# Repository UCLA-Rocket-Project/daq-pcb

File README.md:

# daq-pcb
DAQ PCB

## Preview
Check out the
[super cool HTML preview](http://ucla-rocket-project.github.io/daq-pcb) .

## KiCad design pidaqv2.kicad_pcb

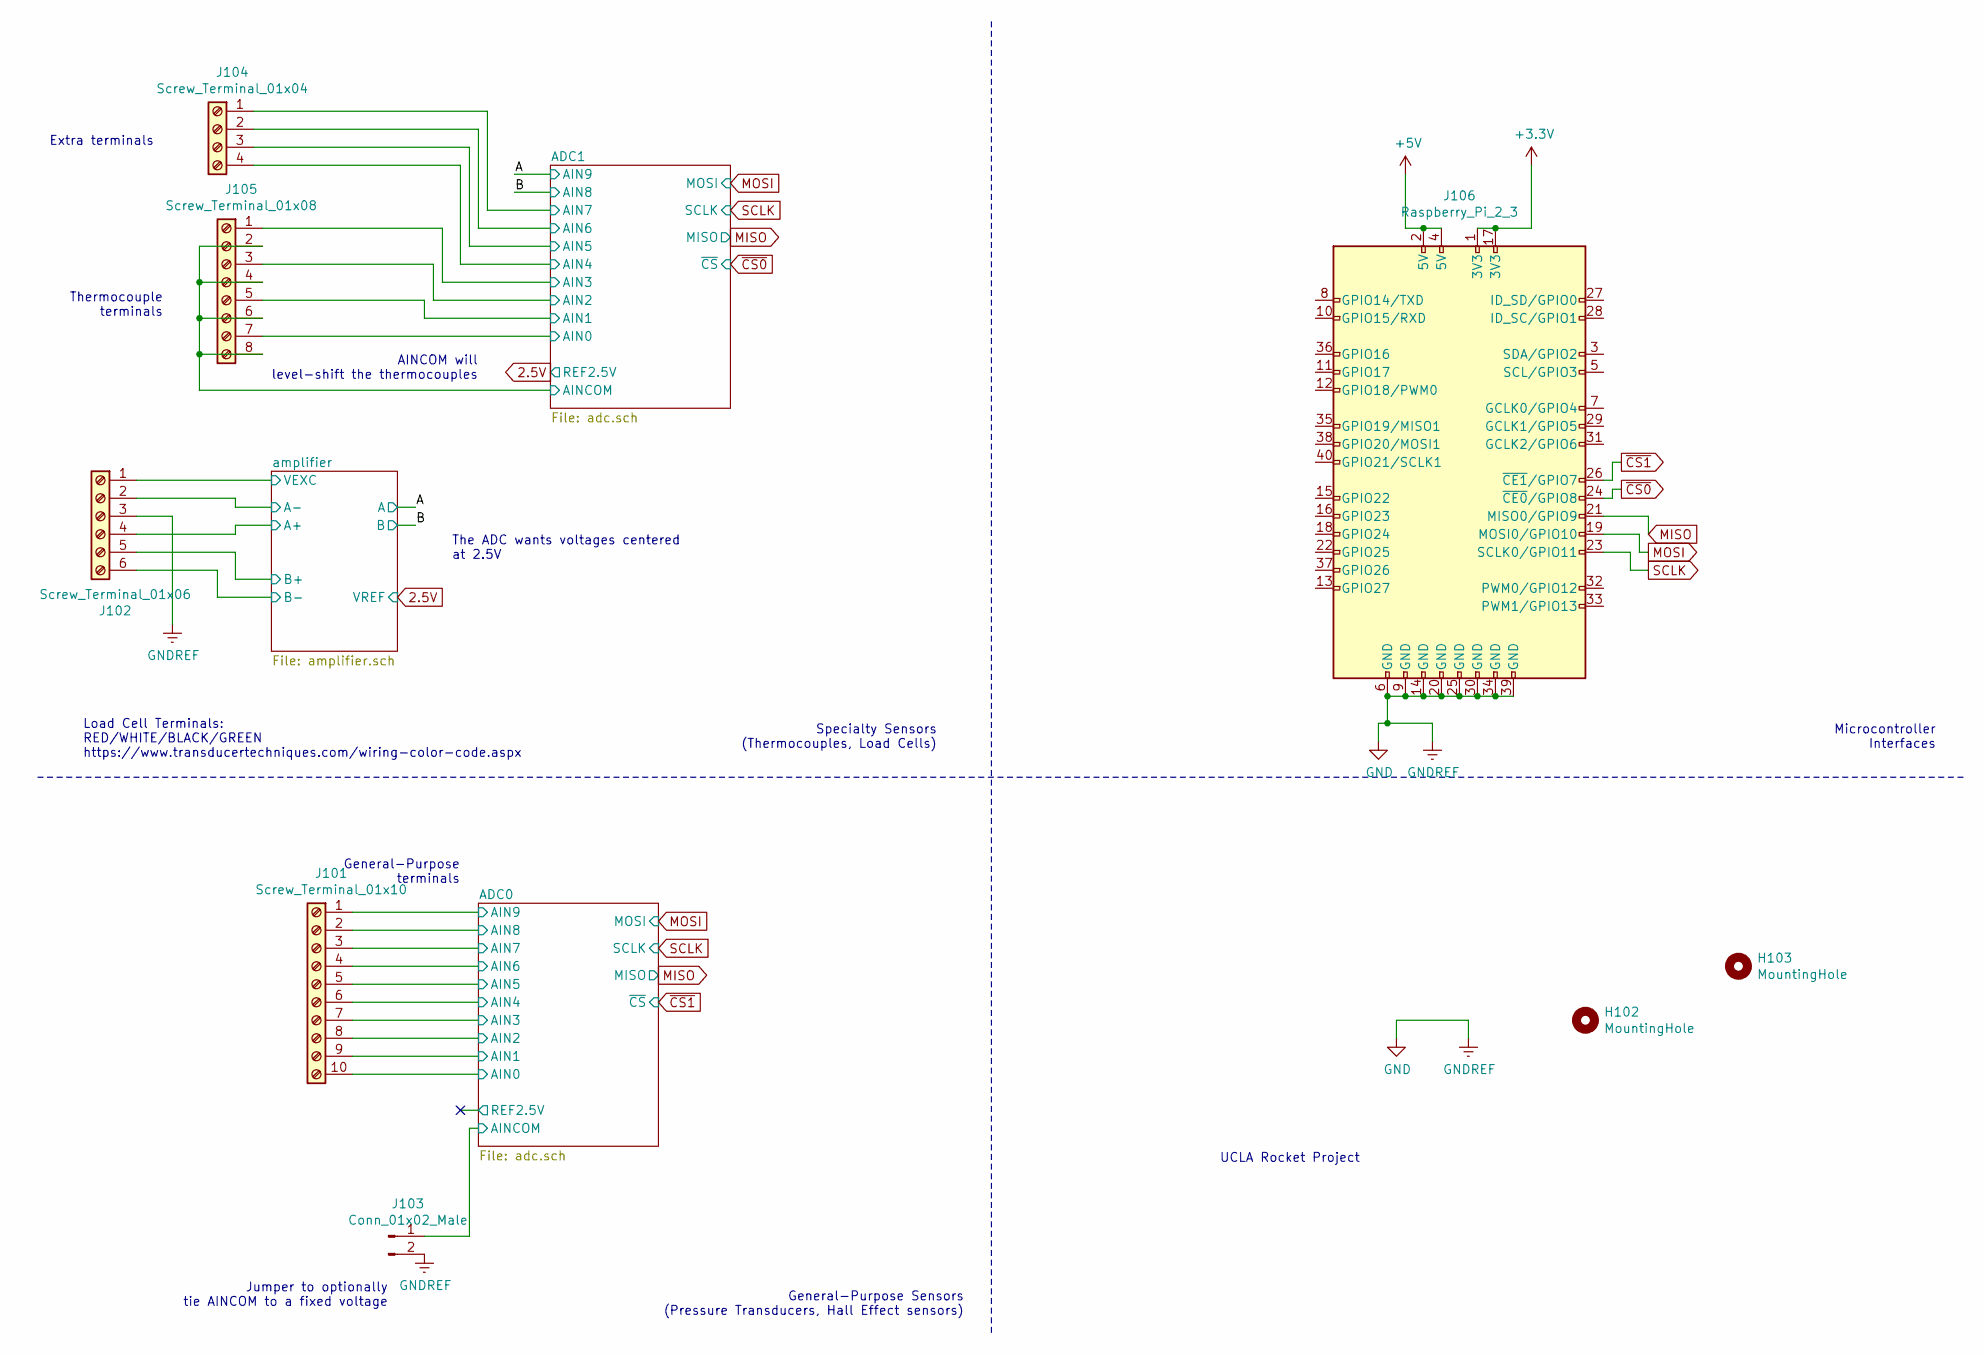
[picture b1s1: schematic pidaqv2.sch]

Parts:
H102, H103: MountingHole; MountingHole_3.2mm_M3_ISO7380
J101: Screw_Terminal_01x10; TerminalBlock_TE_1-282834-0_1x10_P2.54mm_Horizontal
J102: Screw_Terminal_01x06; TerminalBlock_TE_282834-6_1x06_P2.54mm_Horizontal
J103: Conn_01x02_Male; PinHeader_1x02_P2.54mm_Vertical
J104: Screw_Terminal_01x04; TerminalBlock_TE_282834-4_1x04_P2.54mm_Horizontal
J105: Screw_Terminal_01x08; TerminalBlock_TE_282834-8_1x08_P2.54mm_Horizontal
J106: Raspberry_Pi_2_3; PinHeader_2x20_P2.54mm_Vertical

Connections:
+3V3: J106.1 (3V3), J106.17 (3V3); also elsewhere on the board
+5V: J106.2 (5V), J106.4 (5V); also elsewhere on the board
/ADC0/AIN0: J101.10; also elsewhere on the board
/ADC0/AIN1: J101.9; also elsewhere on the board
/ADC0/AIN2: J101.8; also elsewhere on the board
/ADC0/AIN3: J101.7; also elsewhere on the board
/ADC0/AIN4: J101.6; also elsewhere on the board
/ADC0/AIN5: J101.5; also elsewhere on the board
/ADC0/AIN6: J101.4; also elsewhere on the board
/ADC0/AIN7: J101.3; also elsewhere on the board
/ADC0/AIN8: J101.2; also elsewhere on the board
/ADC0/AIN9: J101.1; also elsewhere on the board
/ADC0/AINCOM: J103.1; also elsewhere on the board
/ADC1/AIN0: J105.7; also elsewhere on the board
/ADC1/AIN1: J105.5; also elsewhere on the board
/ADC1/AIN2: J105.3; also elsewhere on the board
/ADC1/AIN3: J105.1; also elsewhere on the board
/ADC1/AIN4: J104.4; also elsewhere on the board
/ADC1/AIN5: J104.3; also elsewhere on the board
/ADC1/AIN6: J104.2; also elsewhere on the board
/ADC1/AIN7: J104.1; also elsewhere on the board
/ADC1/AINCOM: J105.2, J105.4, J105.6, J105.8; also elsewhere on the board
/amplifier/A+: J102.4; also elsewhere on the board
/amplifier/A-: J102.2; also elsewhere on the board
/amplifier/B+: J102.5; also elsewhere on the board
/amplifier/B-: J102.6; also elsewhere on the board
/amplifier/VEXC: J102.1; also elsewhere on the board
GND: J102.3, J103.2, J106.6 (GND), J106.9 (GND), J106.14 (GND), J106.20 (GND), J106.25 (GND), J106.30 (GND), J106.34 (GND), J106.39 (GND); also elsewhere on the board
MISO: J106.21 (MISO0/GPIO9); also elsewhere on the board
MOSI: J106.19 (MOSI0/GPIO10); also elsewhere on the board
SCLK: J106.23 (SCLK0/GPIO11); also elsewhere on the board
~CS0: J106.24 (~CE0~/GPIO8); also elsewhere on the board
~CS1: J106.26 (~CE1~/GPIO7); also elsewhere on the board

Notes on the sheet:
The ADC wants voltages centered at 2.5V
Jumper to optionally tie AINCOM to a fixed voltage
Load Cell Terminals: RED/WHITE/BLACK/GREEN https://www.transducertechniques.com/wiring-color-code.aspx
AINCOM will level-shift the thermocouples
Thermocouple terminals
General-Purpose terminals
UCLA Rocket Project
Specialty Sensors (Thermocouples, Load Cells)
General-Purpose Sensors (Pressure Transducers, Hall Effect sensors)
Microcontroller Interfaces
Extra terminals

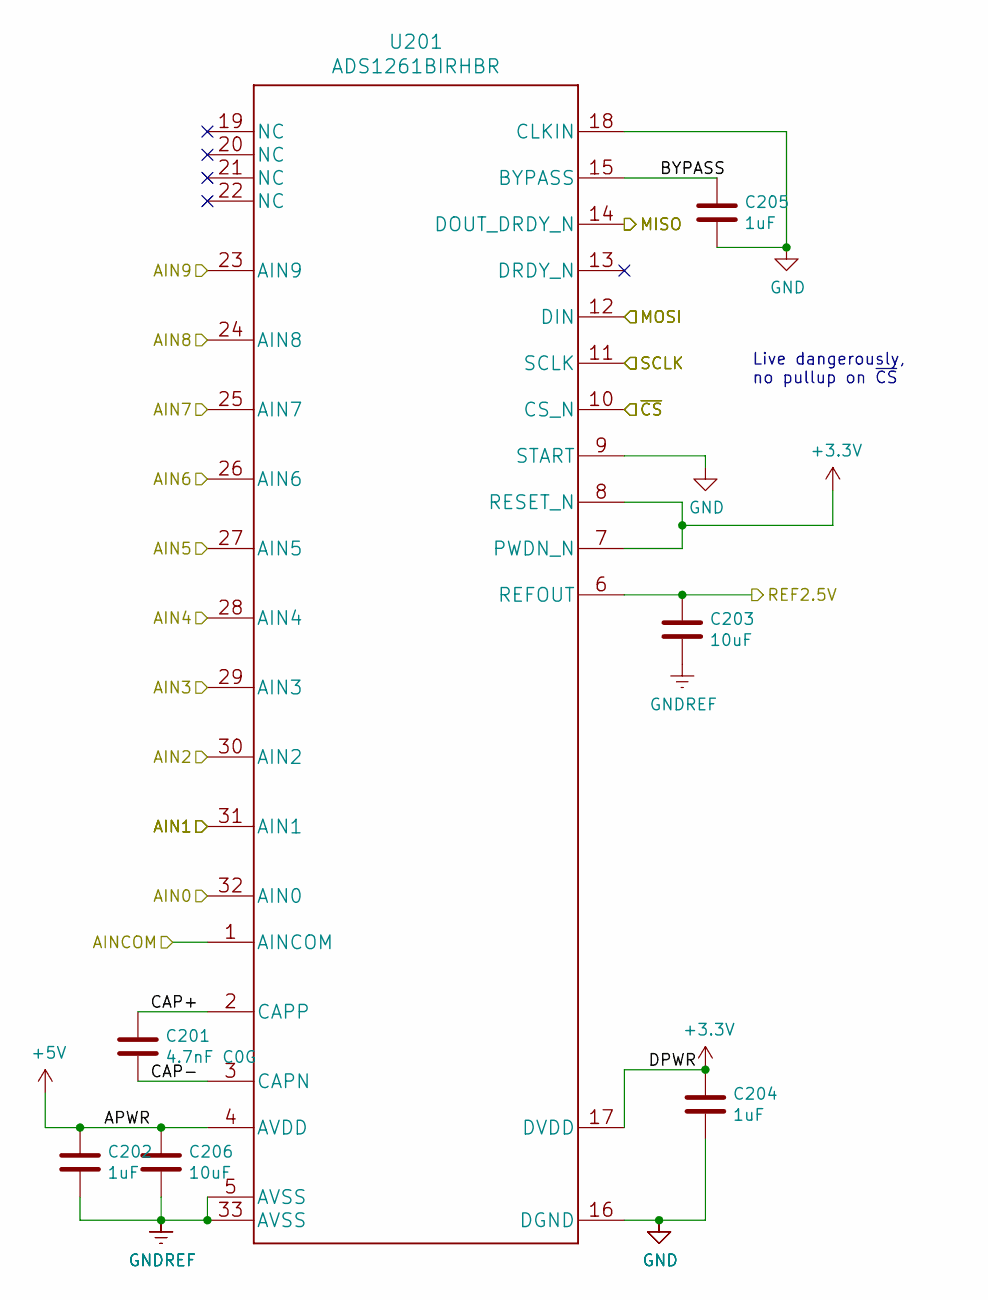
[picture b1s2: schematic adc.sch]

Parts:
C202, C204, C205: 1uF; C_0805_2012Metric_Pad1.15x1.40mm_HandSolder; LCSC C28323
C301: 4.7nF C0G; C_0805_2012Metric_Pad1.15x1.40mm_HandSolder; LCSC C50131
C303, C306: 10uF; C_0805_2012Metric_Pad1.15x1.40mm_HandSolder; LCSC C46653
U301: ADS1261BIRHBR; Texas_S-PVQFN-N32_EP3.45x3.45mm

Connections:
2.5V: C303.1, U301.6 (REFOUT); also elsewhere on the board
+3V3: C204.1, U301.7 (PWDN_N), U301.8 (RESET_N), U301.17 (DVDD); also elsewhere on the board
+5V: C202.1, C306.1, U301.4 (AVDD); also elsewhere on the board
/A: U301.23 (AIN9); also elsewhere on the board
/ADC1/AIN0: U301.32 (AIN0); also elsewhere on the board
/ADC1/AIN1: U301.31 (AIN1); also elsewhere on the board
/ADC1/AIN2: U301.30 (AIN2); also elsewhere on the board
/ADC1/AIN3: U301.29 (AIN3); also elsewhere on the board
/ADC1/AIN4: U301.28 (AIN4); also elsewhere on the board
/ADC1/AIN5: U301.27 (AIN5); also elsewhere on the board
/ADC1/AIN6: U301.26 (AIN6); also elsewhere on the board
/ADC1/AIN7: U301.25 (AIN7); also elsewhere on the board
/ADC1/AINCOM: U301.1 (AINCOM); also elsewhere on the board
/ADC1/CAP+: C301.1, U301.2 (CAPP)
/ADC1/CAP-: C301.2, U301.3 (CAPN)
/B: U301.24 (AIN8); also elsewhere on the board
GND: C202.2, C204.2, C205.2, C303.2, C306.2, U301.5 (AVSS), U301.9 (START), U301.16 (DGND), U301.18 (CLKIN), U301.33 (AVSS); also elsewhere on the board
MISO: U301.14 (DOUT_DRDY_N); also elsewhere on the board
MOSI: U301.12 (DIN); also elsewhere on the board
SCLK: U301.11 (SCLK); also elsewhere on the board
~CS0: U301.10 (CS_N); also elsewhere on the board

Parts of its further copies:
C201: 4.7nF C0G; C_0805_2012Metric_Pad1.15x1.40mm_HandSolder; LCSC C50131
C203, C206: 10uF; C_0805_2012Metric_Pad1.15x1.40mm_HandSolder; LCSC C46653
C302, C304, C305: 1uF; C_0805_2012Metric_Pad1.15x1.40mm_HandSolder; LCSC C28323
U201: ADS1261BIRHBR; Texas_S-PVQFN-N32_EP3.45x3.45mm

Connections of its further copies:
+3V3: C304.1, U201.7 (PWDN_N), U201.8 (RESET_N), U201.17 (DVDD); also elsewhere on the board
+5V: C206.1, C302.1, U201.4 (AVDD); also elsewhere on the board
/ADC0/AIN0: U201.32 (AIN0); also elsewhere on the board
/ADC0/AIN1: U201.31 (AIN1); also elsewhere on the board
/ADC0/AIN2: U201.30 (AIN2); also elsewhere on the board
/ADC0/AIN3: U201.29 (AIN3); also elsewhere on the board
/ADC0/AIN4: U201.28 (AIN4); also elsewhere on the board
/ADC0/AIN5: U201.27 (AIN5); also elsewhere on the board
/ADC0/AIN6: U201.26 (AIN6); also elsewhere on the board
/ADC0/AIN7: U201.25 (AIN7); also elsewhere on the board
/ADC0/AIN8: U201.24 (AIN8); also elsewhere on the board
/ADC0/AIN9: U201.23 (AIN9); also elsewhere on the board
/ADC0/AINCOM: U201.1 (AINCOM); also elsewhere on the board
/ADC0/CAP+: C201.1, U201.2 (CAPP)
/ADC0/CAP-: C201.2, U201.3 (CAPN)
/ADC0/REF2.5V: C203.1, U201.6 (REFOUT)
GND: C203.2, C206.2, C302.2, C304.2, C305.2, U201.5 (AVSS), U201.9 (START), U201.16 (DGND), U201.18 (CLKIN), U201.33 (AVSS); also elsewhere on the board
MISO: U201.14 (DOUT_DRDY_N); also elsewhere on the board
MOSI: U201.12 (DIN); also elsewhere on the board
SCLK: U201.11 (SCLK); also elsewhere on the board
~CS1: U201.10 (CS_N); also elsewhere on the board

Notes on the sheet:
Live dangerously, no pullup on ~CS

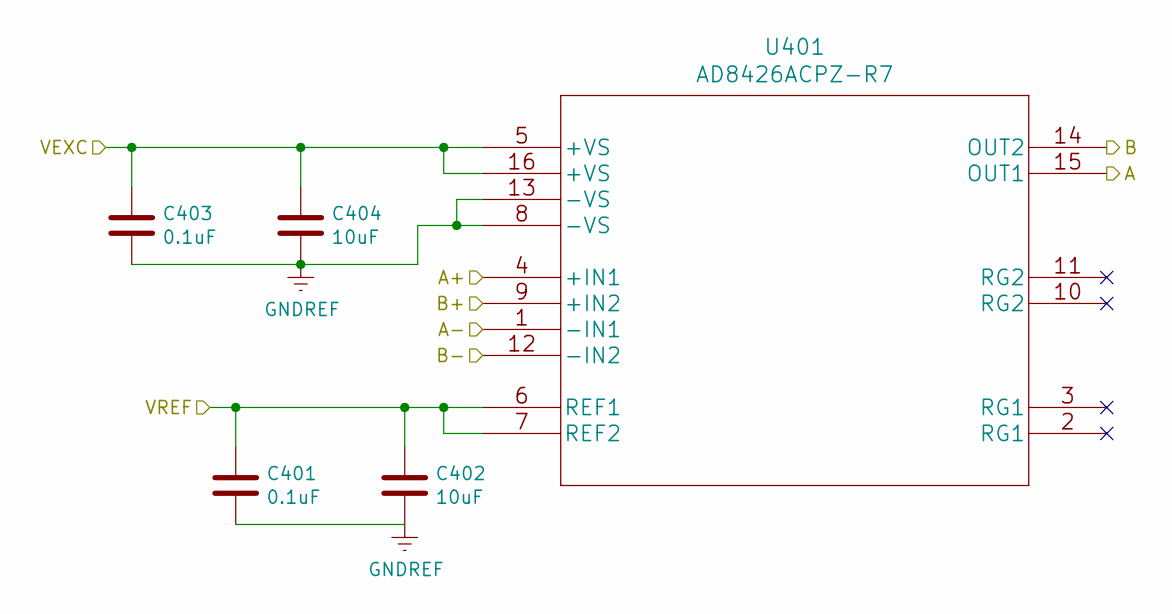
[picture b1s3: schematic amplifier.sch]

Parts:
C401, C403: 0.1uF; C_0805_2012Metric_Pad1.15x1.40mm_HandSolder; LCSC C62912
C402, C404: 10uF; C_0805_2012Metric_Pad1.15x1.40mm_HandSolder; LCSC C46653
U401: AD8426ACPZ-R7

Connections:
2.5V: C401.1, C402.1, U401.6 (REF1), U401.7 (REF2); also elsewhere on the board
/A: U401.15 (OUT1); also elsewhere on the board
/B: U401.14 (OUT2); also elsewhere on the board
/amplifier/A+: U401.4 (+IN1); also elsewhere on the board
/amplifier/A-: U401.1 (-IN1); also elsewhere on the board
/amplifier/B+: U401.9 (+IN2); also elsewhere on the board
/amplifier/B-: U401.12 (-IN2); also elsewhere on the board
/amplifier/VEXC: C403.1, C404.1, U401.5 (+VS), U401.16 (+VS); also elsewhere on the board
GND: C401.2, C402.2, C403.2, C404.2, U401.8 (-VS), U401.13 (-VS); also elsewhere on the board

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
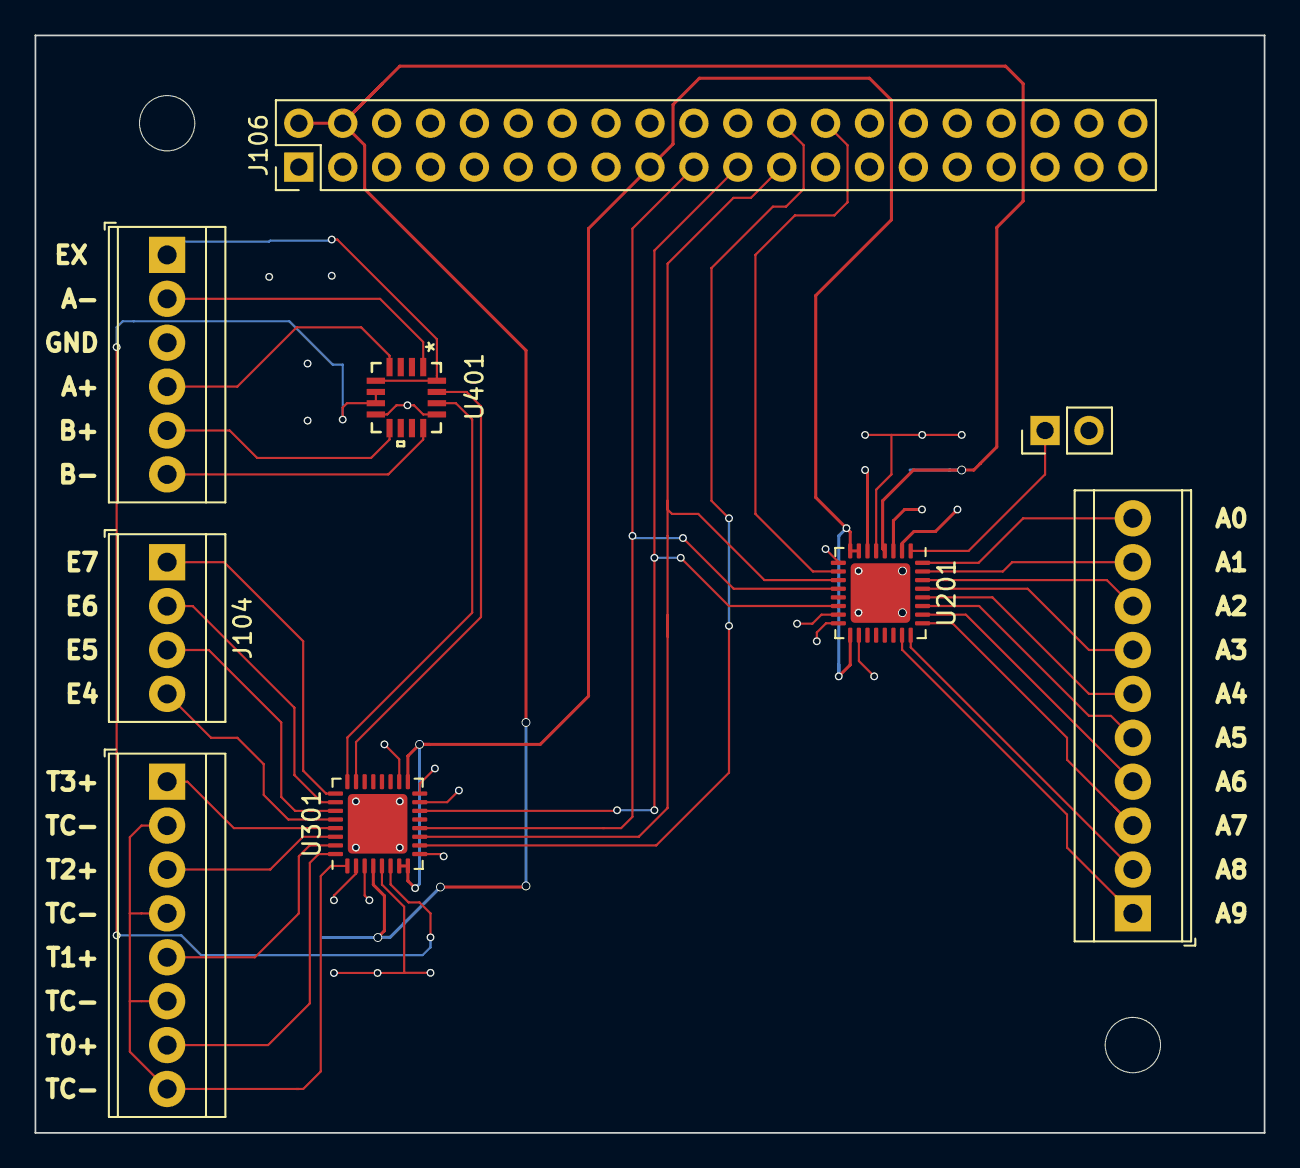
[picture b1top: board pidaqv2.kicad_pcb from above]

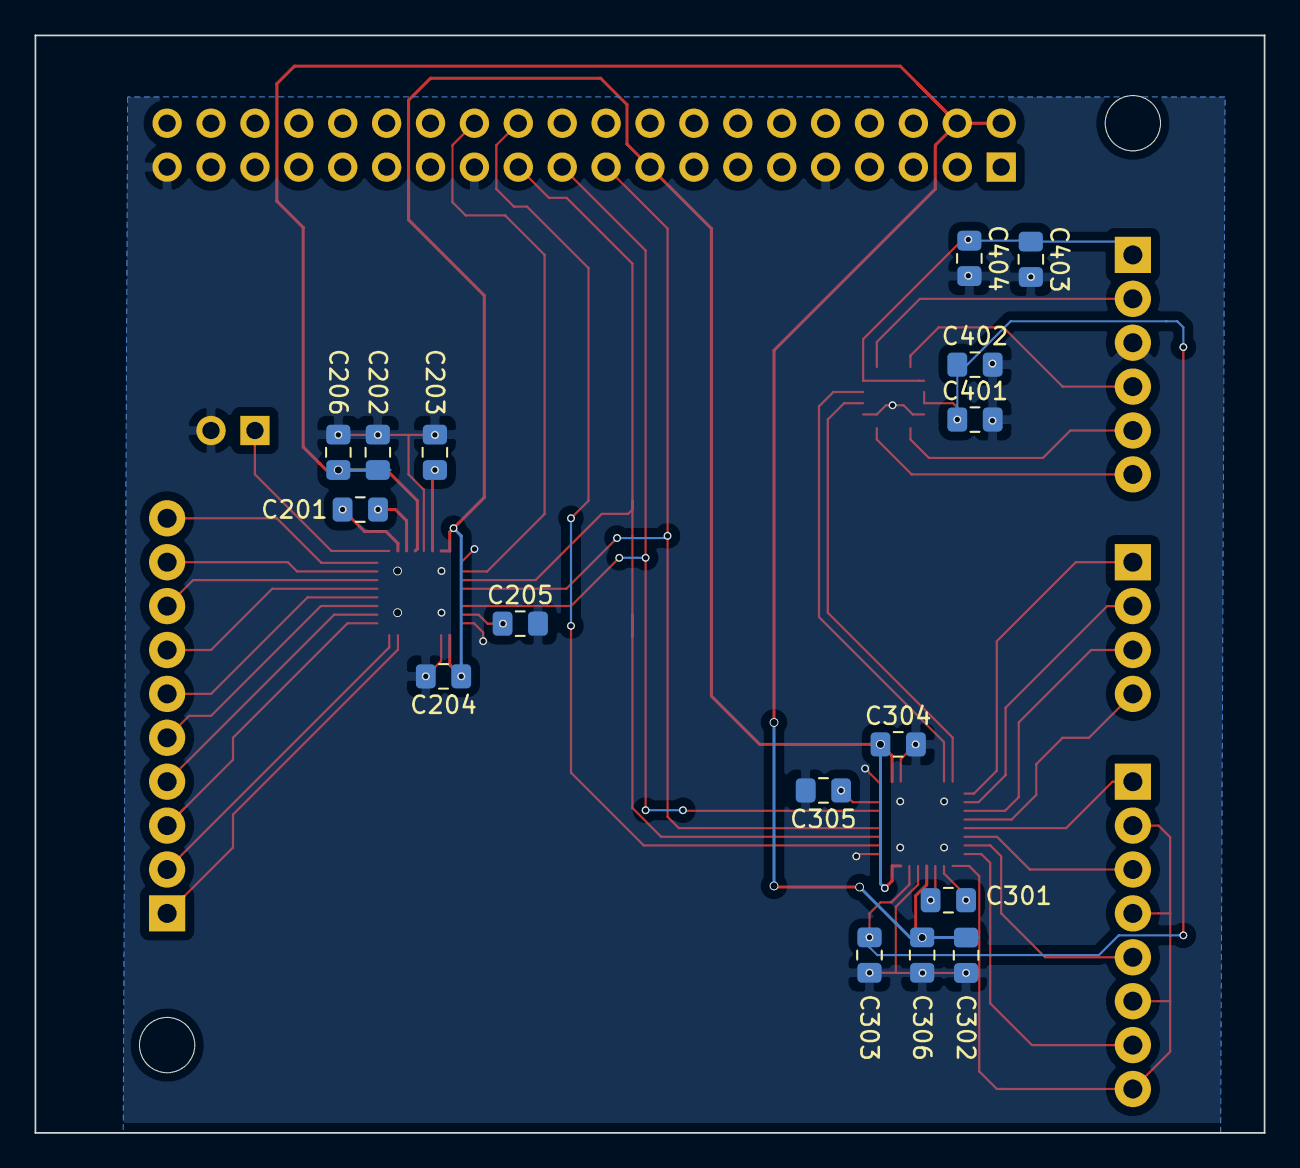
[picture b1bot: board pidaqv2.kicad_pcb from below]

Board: 2 copper layers, 71.1 x 63.5 mm, 27 parts (16 on the bottom side), 43 nets.

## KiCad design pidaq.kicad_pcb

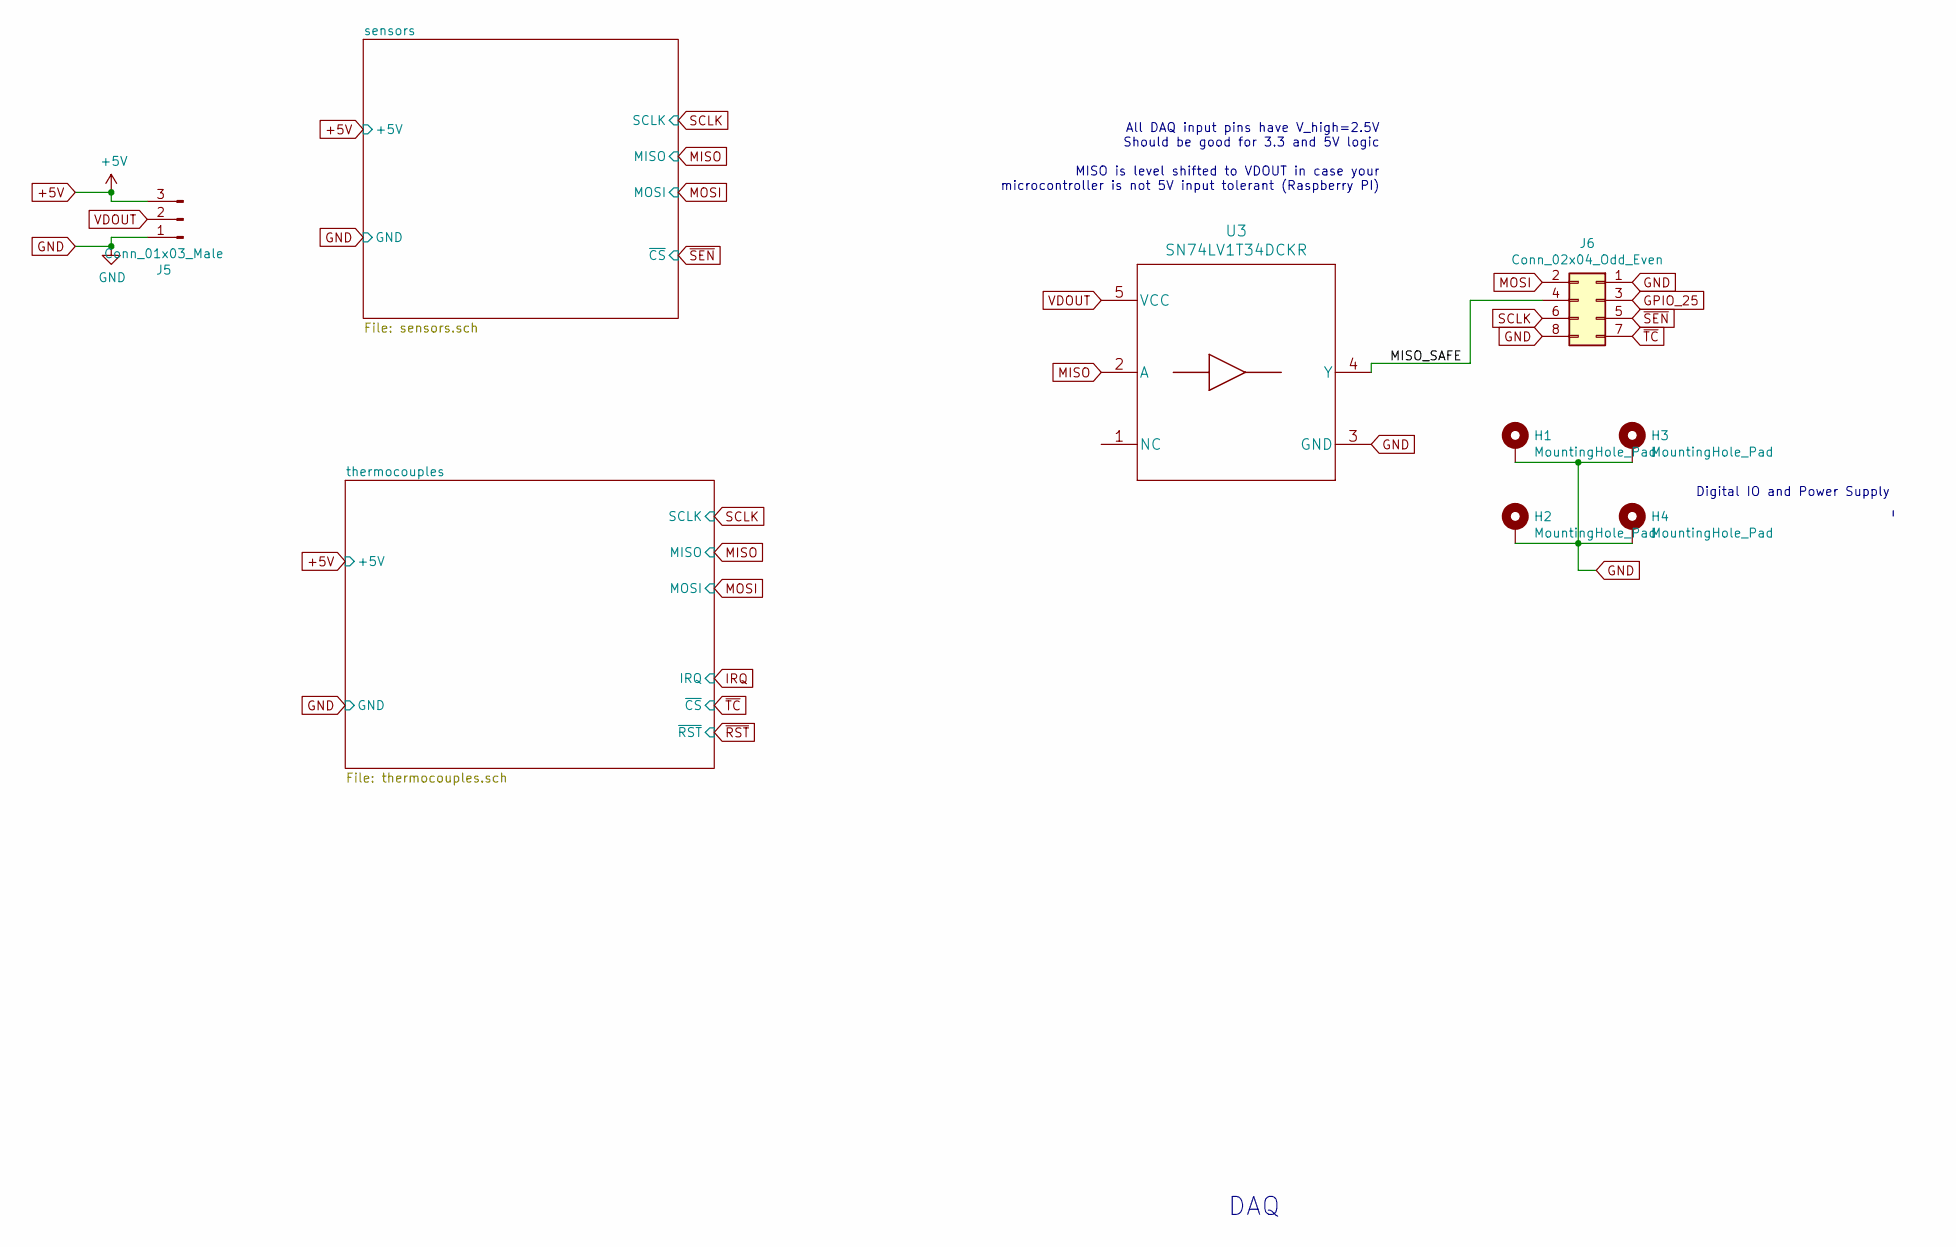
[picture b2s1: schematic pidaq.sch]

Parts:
H1, H2, H3, H4: MountingHole_Pad; MountingHole_3.2mm_M3_Pad_Via
J5: Conn_01x03_Male; PinHeader_1x03_P2.54mm_Vertical
J6: Conn_02x04_Odd_Even; PinSocket_2x04_P2.54mm_Vertical
U3: SN74LV1T34DCKR

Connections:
+5V: J5.3; also elsewhere on the board
/MISO_SAFE: J6.4, U3.4 (Y)
GND: H1.1, H2.1, H3.1, H4.1, J5.1, J6.1, J6.8, U3.3 (GND); also elsewhere on the board
MISO: U3.2 (A); also elsewhere on the board
MOSI: J6.2; also elsewhere on the board
SCLK: J6.6; also elsewhere on the board
VDOUT: J5.2, U3.5 (VCC)
~SEN: J6.5; also elsewhere on the board
~TC: J6.7; also elsewhere on the board

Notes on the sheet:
DAQ
Digital IO and Power Supply
All DAQ input pins have V_high=2.5V Should be good for 3.3 and 5V logic MISO is level shifted to VDOUT in case your microcontroller is not 5V input tolerant (Raspberry PI)

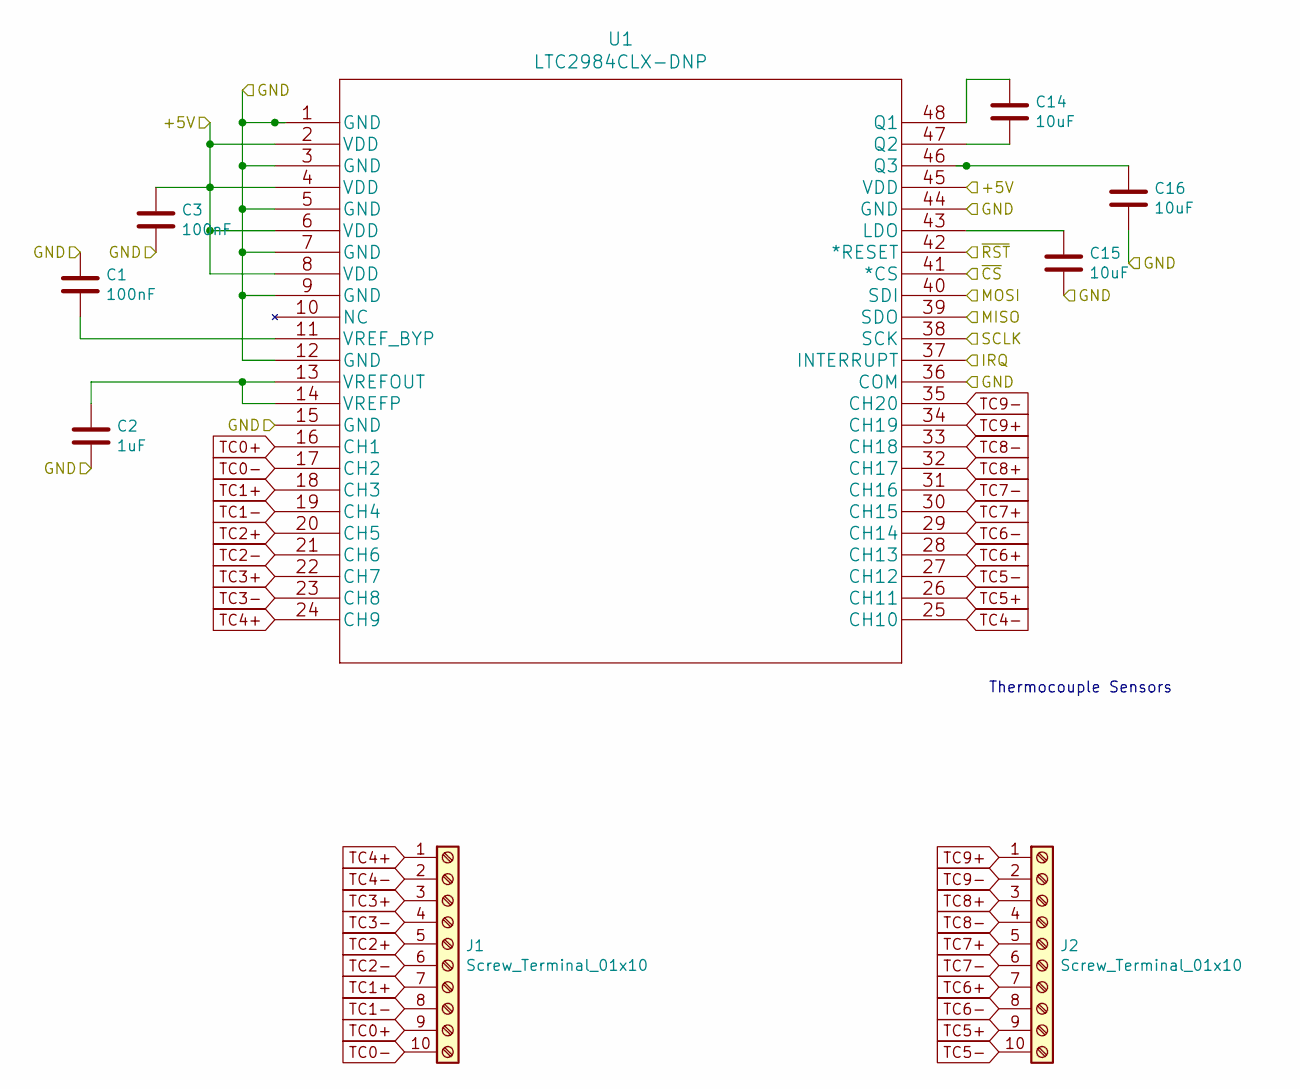
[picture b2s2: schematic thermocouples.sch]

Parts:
C1, C3: 100nF; C_0805_2012Metric_Pad1.15x1.40mm_HandSolder
C2: 1uF; C_0805_2012Metric_Pad1.15x1.40mm_HandSolder
C14, C15, C16: 10uF; C_0805_2012Metric_Pad1.15x1.40mm_HandSolder
J1, J2: Screw_Terminal_01x10; TerminalBlock_Phoenix_MPT-0,5-10-2.54_1x10_P2.54mm_Horizont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
U1: LTC2984CLX-DNP; LTC2984CLX-PBF

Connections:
+5V: C3.1, U1.2 (VDD), U1.4 (VDD), U1.6 (VDD), U1.8 (VDD), U1.45 (VDD); also elsewhere on the board
GND: C1.1, C2.2, C3.2, C15.2, C16.2, U1.1 (GND), U1.3 (GND), U1.5 (GND), U1.7 (GND), U1.9 (GND), U1.12 (GND), U1.15 (GND), U1.36 (COM), U1.44 (GND); also elsewhere on the board
MISO: U1.39 (SDO); also elsewhere on the board
MOSI: U1.40 (SDI); also elsewhere on the board
unnamed: C1.2, U1.11 (VREF_BYP)
unnamed: C2.1, U1.13 (VREFOUT), U1.14 (VREFP)
unnamed: C14.1, U1.48 (Q1)
unnamed: C14.2, U1.47 (Q2)
unnamed: C15.1, U1.43 (LDO)
unnamed: C16.1, U1.46 (Q3)
SCLK: U1.38 (SCK); also elsewhere on the board
TC0+: J1.9, U1.16 (CH1)
TC0-: J1.10, U1.17 (CH2)
TC1+: J1.7, U1.18 (CH3)
TC1-: J1.8, U1.19 (CH4)
TC2+: J1.5, U1.20 (CH5)
TC2-: J1.6, U1.21 (CH6)
TC3+: J1.3, U1.22 (CH7)
TC3-: J1.4, U1.23 (CH8)
TC4+: J1.1, U1.24 (CH9)
TC4-: J1.2, U1.25 (CH10)
TC5+: J2.9, U1.26 (CH11)
TC5-: J2.10, U1.27 (CH12)
TC6+: J2.7, U1.28 (CH13)
TC6-: J2.8, U1.29 (CH14)
TC7+: J2.5, U1.30 (CH15)
TC7-: J2.6, U1.31 (CH16)
TC8+: J2.3, U1.32 (CH17)
TC8-: J2.4, U1.33 (CH18)
TC9+: J2.1, U1.34 (CH19)
TC9-: J2.2, U1.35 (CH20)
~TC: U1.41 (*CS); also elsewhere on the board

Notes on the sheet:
Thermocouple Sensors

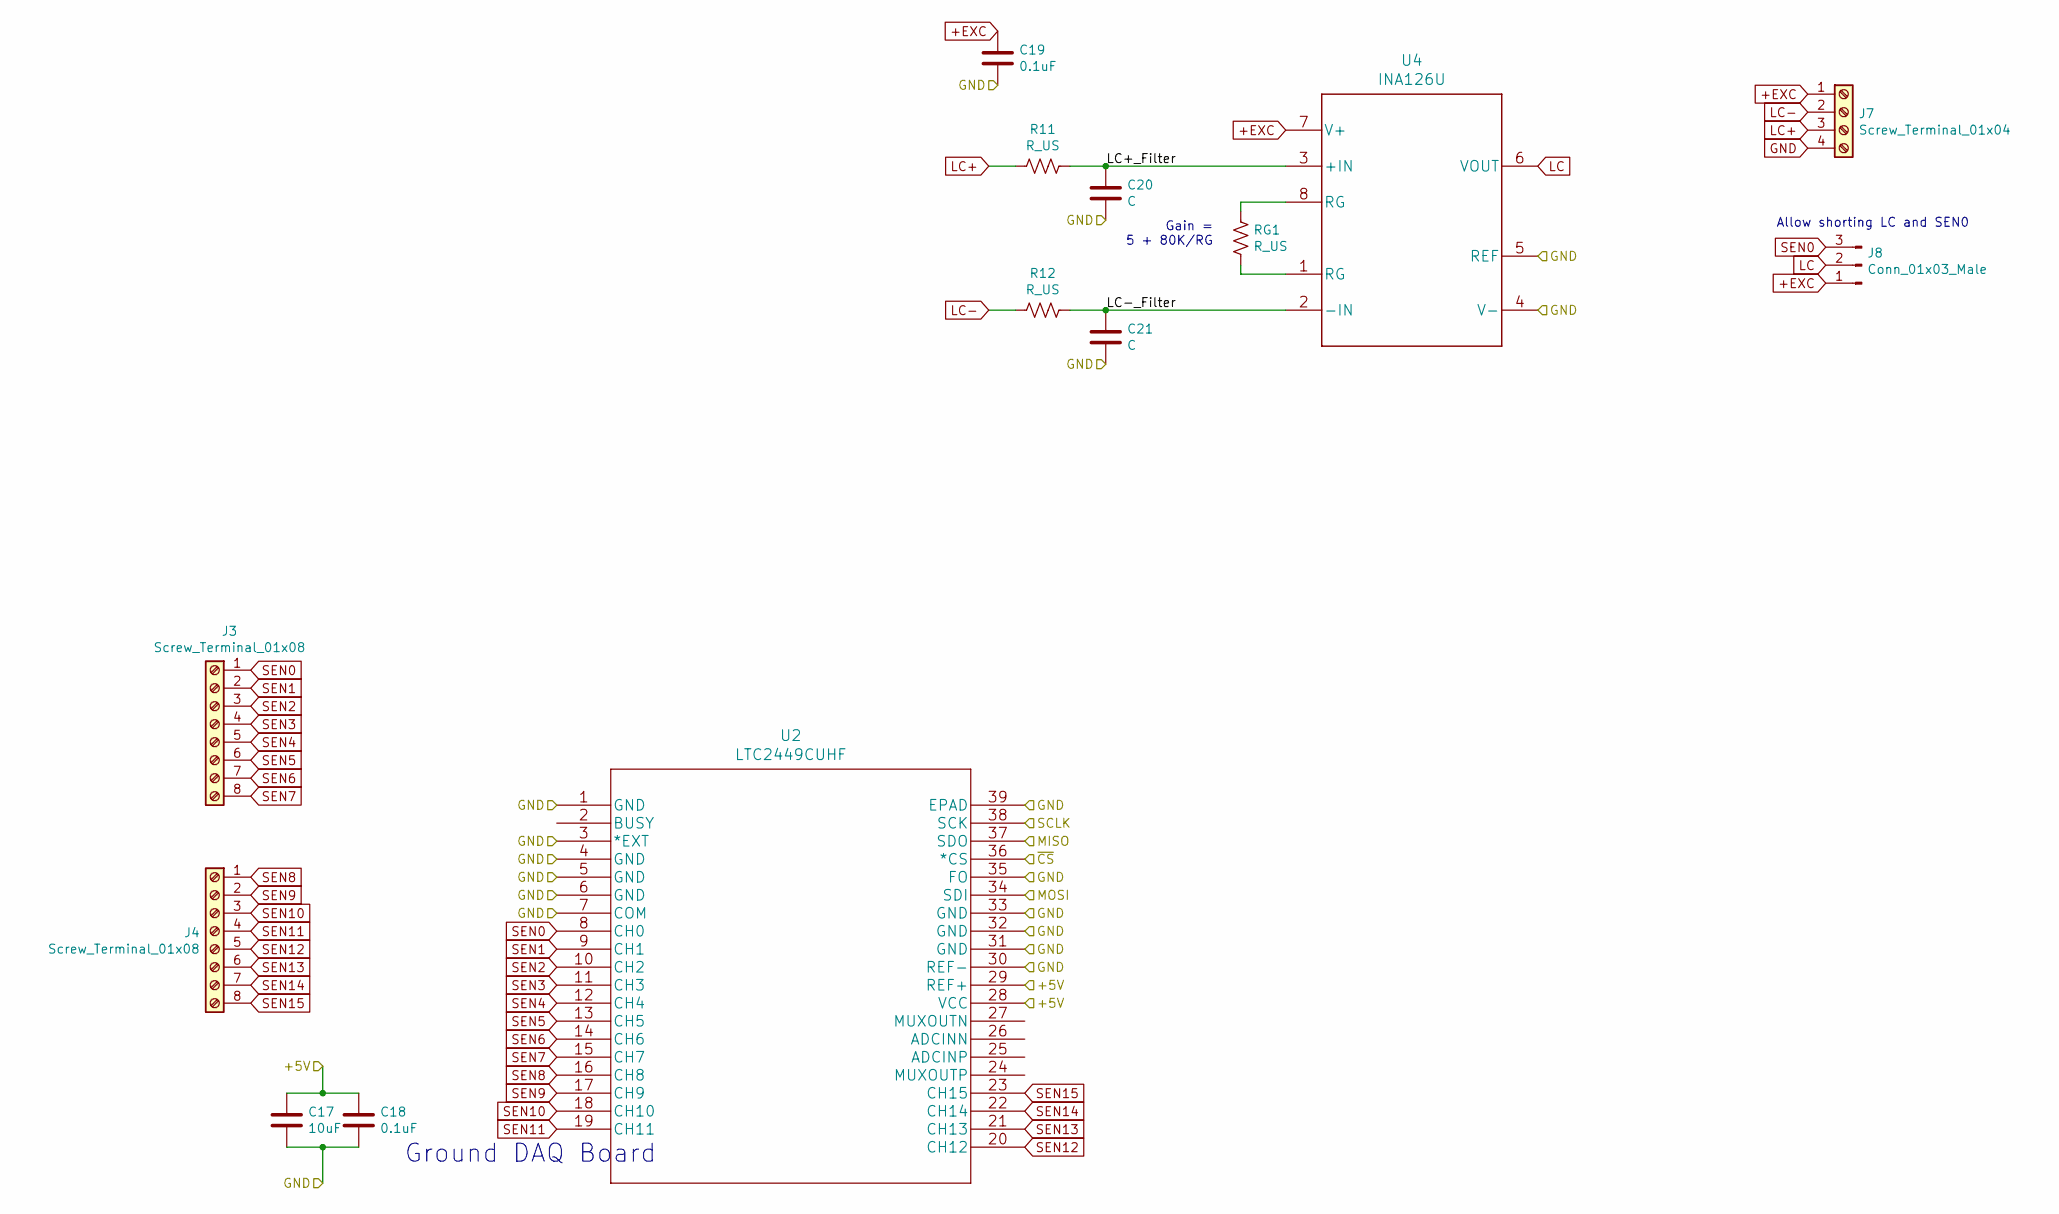
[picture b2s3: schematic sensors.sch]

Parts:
C17: 10uF; C_0805_2012Metric_Pad1.15x1.40mm_HandSolder
C18, C19: 0.1uF; C_0805_2012Metric_Pad1.15x1.40mm_HandSolder
C20, C21: C; C_0805_2012Metric_Pad1.15x1.40mm_HandSolder
J3, J4: Screw_Terminal_01x08; TerminalBlock_Phoenix_MKDS-1,5-8-5.08_1x08_P5.08mm_Horizont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
J7: Screw_Terminal_01x04; TerminalBlock_Phoenix_MKDS-1,5-4-5.08_1x04_P5.08mm_Horizont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
J8: Conn_01x03_Male; PinHeader_1x03_P2.54mm_Vertical
R11, R12: R_US; R_0805_2012Metric_Pad1.15x1.40mm_HandSolder
RG1: R_US; R_Axial_DIN0309_L9.0mm_D3.2mm_P12.70mm_Horizontal
U2: LTC2449CUHF
U4: INA126U

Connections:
+5V: C17.1, C18.1, U2.28 (VCC), U2.29 (REF+); also elsewhere on the board
+EXC: C19.1, J7.1, J8.1, U4.7 (V+)
/sensors/LC+_Filter: C20.1, R11.1, U4.3 (+IN)
/sensors/LC-_Filter: C21.1, R12.1, U4.2 (-IN)
GND: C17.2, C18.2, C19.2, C20.2, C21.2, J7.4, U2.1 (GND), U2.3 (*EXT), U2.4 (GND), U2.5 (GND), U2.6 (GND), U2.7 (COM), U2.30 (REF-), U2.31 (GND), U2.32 (GND), U2.33 (GND), U2.35 (FO), U2.39 (EPAD), U4.4 (V-), U4.5 (REF); also elsewhere on the board
LC: J8.2, U4.6 (VOUT)
LC+: J7.3, R11.2
LC-: J7.2, R12.2
MISO: U2.37 (SDO); also elsewhere on the board
MOSI: U2.34 (SDI); also elsewhere on the board
unnamed: RG1.1, U4.8 (RG)
unnamed: RG1.2, U4.1 (RG)
SCLK: U2.38 (SCK); also elsewhere on the board
SEN0: J3.1, J8.3, U2.8 (CH0)
SEN1: J3.2, U2.9 (CH1)
SEN2: J3.3, U2.10 (CH2)
SEN3: J3.4, U2.11 (CH3)
SEN4: J3.5, U2.12 (CH4)
SEN5: J3.6, U2.13 (CH5)
SEN6: J3.7, U2.14 (CH6)
SEN7: J3.8, U2.15 (CH7)
SEN8: J4.1, U2.16 (CH8)
SEN9: J4.2, U2.17 (CH9)
SEN10: J4.3, U2.18 (CH10)
SEN11: J4.4, U2.19 (CH11)
SEN12: J4.5, U2.20 (CH12)
SEN13: J4.6, U2.21 (CH13)
SEN14: J4.7, U2.22 (CH14)
SEN15: J4.8, U2.23 (CH15)
~SEN: U2.36 (*CS); also elsewhere on the board

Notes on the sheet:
Ground DAQ Board
Gain = 5 + 80K/RG
Allow shorting LC and SEN0

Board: 2 copper layers, 30 parts (0 on the bottom side), 59 nets, no tracks yet.

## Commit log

2020-05-30 Create LICENSE
2020-05-30 finished silkscreen
2020-05-30 removed silkscreen offset
2020-05-30 add datasheets
2020-05-31 add html preview
2020-05-31 closing edits for pcb
2020-05-31 added more bom details
2020-06-02 convert uF to nF for better BOM compatibility
2020-06-02 add level shifters to MISO
2020-06-03 reversed screw terminal symbols
2020-06-04 turn screw holes into plated ones for more grounding
2020-06-04 removed an artifact old schematic
2020-06-05 updated ics and load cell amplifier
2020-06-05 completed design 2.0
2020-06-05 updated silkscreen and removed old adc
2020-06-05 updated html preview
2020-06-06 added low pass filter to load cell inputs
2020-06-08 touched up silkscreen and trace spacing
2020-06-14 moved vias into pads
2020-06-15 updated preview
2020-06-15 pcb size reduced to 3x3in
2020-08-15 initial commit v2
2020-08-15 added layout and online BOM viewer
2020-08-15 silkscreen added
2020-08-16 redid SPI traces
2020-08-21 SPI layout cleaned up further
2020-08-30 ads1261
2020-09-05 last highfreq
2020-09-22 boi did i cut up that ground plane
2020-09-22 remove git artifact
2020-09-22 add html preview artifacts
2020-09-24 add silkscreen labels
2020-10-02 placed general sensors chip
2020-10-03 placed digital gnd plane
2020-10-03 temporarily complete
2020-10-03 without silkscreen
2020-10-03 update website
2020-10-18 set up for reviewers
2020-12-01 Switched out arduino for raspberry pi
2020-12-03 slid the header to the right, and set IO to 3.3V
2020-12-08 removed alias of project

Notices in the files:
parts and their libraries:
Copyright 2016 Accelerated Designs. All rights reserved.
